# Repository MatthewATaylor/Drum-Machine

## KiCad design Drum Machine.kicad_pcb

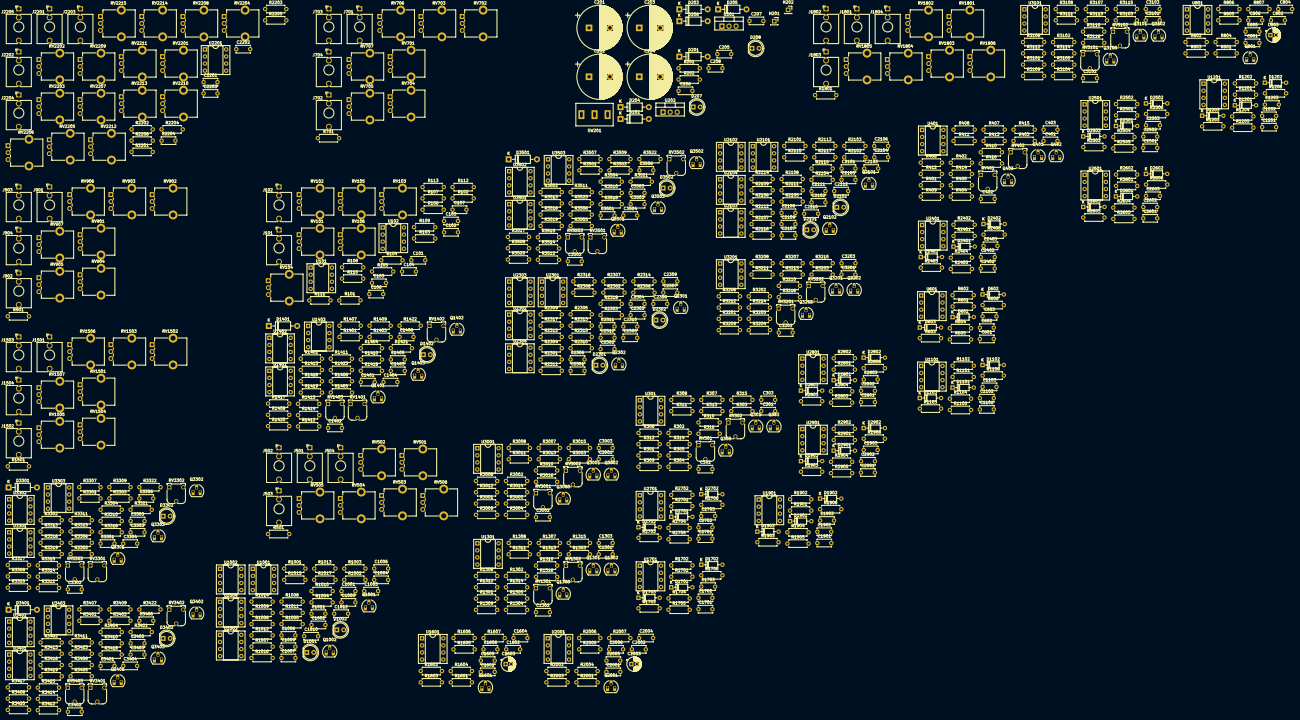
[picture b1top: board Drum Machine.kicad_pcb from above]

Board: 2 copper layers, 752 parts (0 on the bottom side), 443 nets, no tracks yet.

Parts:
C101, C601, C804, C1101, C1201, C1604, C1701, C1901, C2004, C2401, C2501, C2601, C2701, C2801, C2901: 10n; C_Disc_D5.0mm_W2.5mm_P5.00mm
C102, C103, C1008, C1011, C2108, C2111, C2201, C2308, C2311: 1n; C_Disc_D5.0mm_W2.5mm_P5.00mm
C104, C105, C106, C107, C301, C302, C401, C402, C602, C801, C802, C1002, C1003, C1004, C1005, C1006, C1007, C1009, C1010, C1102, C1202, C1301, C1302, C1401, C1402, C1403, C1404, C1405, C1406, C1601, C1602, C1702, C1902, C2001, C2002, C2102, C2103, C2104, C2105, C2106, C2107, C2109, C2110, C2202, C2203, C2204, C2302, C2303, C2304, C2305, C2306, C2307, C2309, C2310, C2402, C2502, C2602, C2702, C2802, C2902, C3001, C3002, C3101, C3102, C3201, C3202, C3301, C3302, C3303, C3304, C3305, C3306, C3401, C3402, C3403, C3404, C3405, C3406, C3501, C3502, C3503, C3504, C3505, C3506: 0.1u; C_Disc_D5.0mm_W2.5mm_P5.00mm
C201, C202, C203, C204: 2200u; CP_Radial_D16.0mm_P7.50mm
C205, C206, C207, C208: 1u; C_Disc_D5.0mm_W2.5mm_P5.00mm
C303, C403, C603, C1103, C1203, C1303, C1703, C1903, C2403, C2503, C2603, C2703, C2803, C2903, C3003, C3103, C3203: 10u; C_Disc_D5.0mm_W2.5mm_P5.00mm
C803, C1603, C2003: 100u; CP_Radial_D5.0mm_P2.00mm
C805, C806, C1605, C1606, C2005, C2006: 220n; C_Disc_D5.0mm_W2.5mm_P5.00mm
C1001, C2101, C2301: 4.7n; C_Disc_D5.0mm_W2.5mm_P5.00mm
C1012, C2112, C2312: 0.47u; C_Disc_D5.0mm_W2.5mm_P5.00mm
D201, D202, D203, D204, D205, D206, D1401, D3301, D3401, D3501: 1N5819; D_DO-41_SOD81_P10.16mm_Horizontal
D207, D208, D1001, D1002, D1402, D2101, D2102, D2301, D2302, D3302, D3402, D3502: LED; LED_D5.0mm
D601, D602, D603, D1101, D1102, D1103, D1201, D1202, D1203, D1701, D1702, D1703, D1901, D1902, D1903, D2401, D2402, D2403, D2501, D2502, D2503, D2601, D2602, D2603, D2701, D2702, D2703, D2801, D2802, D2803, D2901, D2902, D2903: 1N4148; D_DO-35_SOD27_P7.62mm_Horizontal
H201, H202: MountingHole_Pad; PinSocket_1x01_P2.54mm_Vertical
J101, J102, J501, J502, J503, J504, J701, J702, J703, J704, J901, J902, J903, J904, J1501, J1502, J1503, J1504, J1801, J1802, J1803, J1804, J2201, J2202, J2203, J2204, J2205: AudioJack2_SwitchT; Jack_3.5mm_QingPu_WQP-PJ398SM_Vertical_CircularHoles
Q301, Q302, Q303, Q401, Q402, Q403, Q1301, Q1302, Q1303, Q1401, Q1402, Q1403, Q3001, Q3002, Q3003, Q3101, Q3102, Q3103, Q3201, Q3202, Q3203, Q3301, Q3302, Q3303, Q3401, Q3402, Q3403, Q3501, Q3502, Q3503: 2N3904; TO-92_HandSolder
Q801, Q1601, Q2001: BC548; TO-92_HandSolder
Q1001, Q1002, Q2101, Q2102, Q2301, Q2302: BC558; TO-92_HandSolder
R101, R102, R103, R104, R105, R106, R107, R306, R406, R601, R602, R603, R604, R802, R803, R805, R1001, R1002, R1101, R1102, R1103, R1104, R1201, R1202, R1203, R1204, R1306, R1401, R1402, R1403, R1405, R1406, R1407, R1408, R1412, R1602, R1603, R1605, R1701, R1702, R1703, R1704, R1901, R1902, R1903, R1904, R2002, R2003, R2005, R2101, R2102, R2201, R2202, R2203, R2301, R2302, R2303, R2401, R2402, R2403, R2404, R2501, R2502, R2503, R2504, R2601, R2602, R2603, R2604, R2701, R2702, R2703, R2704, R2801, R2802, R2803, R2804, R2901, R2902, R2903, R2904, R3006, R3106, R3206, R3301, R3302, R3303, R3305, R3306, R3307, R3308, R3312, R3401, R3402, R3403, R3405, R3406, R3407, R3408, R3412, R3501, R3502, R3503, R3505, R3506, R3507, R3508, R3512: 100k; R_Axial_DIN0207_L6.3mm_D2.5mm_P7.62mm_Horizontal
R108, R110, R301, R401, R1301, R2204, R2205, R3001, R3101, R3201: 220k; R_Axial_DIN0207_L6.3mm_D2.5mm_P7.62mm_Horizontal
R109: 5.6k; R_Axial_DIN0207_L6.3mm_D2.5mm_P7.62mm_Horizontal
R111: 1.5k; R_Axial_DIN0207_L6.3mm_D2.5mm_P7.62mm_Horizontal
R112, R113, R302, R402, R501, R701, R901, R1302, R1501, R1801, R2206, R3002, R3102, R3202: 1k; R_Axial_DIN0207_L6.3mm_D2.5mm_P7.62mm_Horizontal
R201, R202: 33k; R_Axial_DIN0207_L6.3mm_D2.5mm_P7.62mm_Horizontal
R303, R304, R403, R404, R1303, R1304, R1411, R3003, R3004, R3103, R3104, R3203, R3204, R3311, R3411, R3511: 470k; R_Axial_DIN0207_L6.3mm_D2.5mm_P7.62mm_Horizontal
R305, R307, R405, R407, R1305, R1307, R3005, R3007, R3105, R3107, R3205, R3207: 150k; R_Axial_DIN0207_L6.3mm_D2.5mm_P7.62mm_Horizontal
R308, R311, R312, R315, R408, R411, R412, R415, R1308, R1311, R1312, R1315, R3008, R3011, R3012, R3015, R3108, R3111, R3112, R3115, R3208, R3211, R3212, R3215: 22k; R_Axial_DIN0207_L6.3mm_D2.5mm_P7.62mm_Horizontal
R309, R310, R316, R409, R410, R416, R1006, R1009, R1010, R1011, R1012, R1016, R1017, R1309, R1310, R1316, R1414, R1417, R2106, R2109, R2110, R2111, R2112, R2116, R2117, R2307, R2310, R2311, R2312, R2313, R2317, R2318, R3009, R3010, R3016, R3109, R3110, R3116, R3209, R3210, R3216, R3314, R3317, R3414, R3417, R3514, R3517: 10k; R_Axial_DIN0207_L6.3mm_D2.5mm_P7.62mm_Horizontal
R313, R314, R413, R414, R1004, R1313, R1314, R1410, R2104, R2305, R3013, R3014, R3113, R3114, R3213, R3214, R3310, R3410, R3510: 330k; R_Axial_DIN0207_L6.3mm_D2.5mm_P7.62mm_Horizontal
R605, R1105, R1205, R1416, R1705, R1905, R2405, R2505, R2605, R2705, R2805, R2905, R3316, R3416, R3516: 15k; R_Axial_DIN0207_L6.3mm_D2.5mm_P7.62mm_Horizontal
R606, R1106, R1206, R1706, R1906, R2406, R2506, R2606, R2706, R2806, R2906: 470; R_Axial_DIN0207_L6.3mm_D2.5mm_P7.62mm_Horizontal
R801, R804, R806, R1005, R1601, R1604, R1606, R2001, R2004, R2006, R2105, R2306: 4.7k; R_Axial_DIN0207_L6.3mm_D2.5mm_P7.62mm_Horizontal
R807, R1404, R1409, R1607, R2007, R3304, R3309, R3404, R3409, R3504, R3509: 47k; R_Axial_DIN0207_L6.3mm_D2.5mm_P7.62mm_Horizontal
R1003, R1014, R2103, R2114, R2304, R2315: 2.2k; R_Axial_DIN0207_L6.3mm_D2.5mm_P7.62mm_Horizontal
R1007, R1008, R1013, R1015, R1413, R2107, R2108, R2113, R2115, R2308, R2309, R2314, R2316, R3313, R3413, R3513: 220; R_Axial_DIN0207_L6.3mm_D2.5mm_P7.62mm_Horizontal
R1415, R3315, R3415, R3515: 330; R_Axial_DIN0207_L6.3mm_D2.5mm_P7.62mm_Horizontal
R1418, R1419, R3318, R3319, R3418, R3419, R3518, R3519: 7.5k; R_Axial_DIN0207_L6.3mm_D2.5mm_P7.62mm_Horizontal
R1420, R1421, R1422, R3320, R3321, R3322, R3420, R3421, R3422, R3520, R3521, R3522: 680k; R_Axial_DIN0207_L6.3mm_D2.5mm_P7.62mm_Horizontal
R1423, R3323, R3423, R3523: 75k; R_Axial_DIN0207_L6.3mm_D2.5mm_P7.62mm_Horizontal
RV101, RV102, RV103, RV104, RV105, RV106, RV501, RV502, RV503, RV504, RV505, RV506, RV701, RV702, RV703, RV706, RV707, RV901, RV902, RV903, RV906, RV907, RV1501, RV1502, RV1503, RV1506, RV1507, RV1801, RV1802, RV1803, RV1804, RV1805, RV1806, RV2202, RV2203, RV2204, RV2205, RV2206, RV2207, RV2208, RV2210, RV2211, RV2213, RV2214, RV2215: 50k; Potentiometer_Alpha_RD901F-40-00D_Single_Vertical_CircularH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
RV301, RV302, RV401, RV402, RV1301, RV1302, RV1401, RV1402, RV1403, RV3001, RV3002, RV3101, RV3102, RV3201, RV3202, RV3301, RV3302, RV3303, RV3401, RV3402, RV3403, RV3501, RV3502, RV3503: 10k; Potentiometer_Runtron_RM-065_Vertical_Improved
RV704, RV705, RV904, RV905, RV1504, RV1505: 1M; Potentiometer_Alpha_RD901F-40-00D_Single_Vertical_CircularH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
RV2201, RV2209, RV2212: 100k; Potentiometer_Alpha_RD901F-40-00D_Single_Vertical_CircularH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
SW201: SW_SPDT; MTS-102_MTS-103_MTS-112_MTS-113_MTS-123
U101, U102, U301, U401, U801, U1001, U1002, U1301, U1401, U1402, U1403, U1601, U2001, U2101, U2102, U2201, U2301, U2302, U3001, U3101, U3201, U3301, U3302, U3303, U3401, U3402, U3403, U3501, U3502, U3503: TL072; DIP-8_W7.62mm_Socket
U201: LM7812_TO220; TO-220-3_Vertical
U202: LM7912_TO220; TO-220-3_Vertical
U601, U1101, U1201, U1701, U1901, U2401, U2501, U2601, U2701, U2801, U2901: LM358; DIP-8_W7.62mm_Socket
U1003, U1004, U2103, U2104, U2303, U2304: CA3080; DIP-8_W7.62mm_Socket

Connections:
+12V: C104.1, C106.1, C207.1, C301.1, C401.1, C602.1, C801.1, C1002.1, C1004.1, C1007.2, C1010.2, C1102.1, C1202.1, C1301.1, C1401.1, C1403.1, C1405.1, C1601.1, C1702.1, C1902.1, C2001.1, C2102.1, C2104.1, C2107.2, C2110.2, C2202.1, C2302.1, C2304.1, C2307.2, C2310.2, C2402.1, C2502.1, C2602.1, C2702.1, C2802.1, C2902.1, C3001.1, C3101.1, C3201.1, C3301.1, C3303.1, C3305.1, C3401.1, C3403.1, C3405.1, C3501.1, C3503.1, C3505.1, D203.2 (A), D205.1 (K), D207.2 (A), R604.1, R801.1, R1104.1, R1204.1, R1414.1, R1417.1, R1601.1, R1704.1, R1904.1, R2001.1, R2404.1, R2504.1, R2604.1, R2704.1, R2804.1, R2904.1, R3314.1, R3317.1, R3414.1, R3417.1, R3514.1, R3517.1, RV301.2, RV302.1, RV401.2, RV402.1, RV501.1, RV702.1, RV902.1, RV1301.2, RV1302.1, RV1403.1, RV1502.1, RV1801.1, RV2203.1, RV2206.1, RV3001.2, RV3002.1, RV3101.2, RV3102.1, RV3201.2, RV3202.1, RV3303.1, RV3403.1, RV3503.1, U101.8 (V+), U102.8 (V+), U201.3 (VO), U301.8 (V+), U401.8 (V+), U601.8 (V+), U801.8 (V+), U1001.8 (V+), U1002.8 (V+), U1003.7 (V+), U1004.7 (V+), U1101.8 (V+), U1201.8 (V+), U1301.8 (V+), U1401.8 (V+), U1402.8 (V+), U1403.8 (V+), U1601.8 (V+), U1701.8 (V+), U1901.8 (V+), U2001.8 (V+), U2101.8 (V+), U2102.8 (V+), U2103.7 (V+), U2104.7 (V+), U2201.8 (V+), U2301.8 (V+), U2302.8 (V+), U2303.7 (V+), U2304.7 (V+), U2401.8 (V+), U2501.8 (V+), U2601.8 (V+), U2701.8 (V+), U2801.8 (V+), U2901.8 (V+), U3001.8 (V+), U3101.8 (V+), U3201.8 (V+), U3301.8 (V+), U3302.8 (V+), U3303.8 (V+), U3401.8 (V+), U3402.8 (V+), U3403.8 (V+), U3501.8 (V+), U3502.8 (V+), U3503.8 (V+)
-12V: C105.1, C107.1, C208.2, C302.1, C402.1, C802.1, C1003.1, C1005.1, C1006.2, C1009.2, C1302.1, C1402.1, C1404.1, C1406.1, C1602.1, C2002.1, C2103.1, C2105.1, C2106.2, C2109.2, C2203.1, C2303.1, C2305.1, C2306.2, C2309.2, C3002.1, C3102.1, C3202.1, C3302.1, C3304.1, C3306.1, C3402.1, C3404.1, C3406.1, C3502.1, C3504.1, C3506.1, D204.1 (K), D206.2 (A), D208.1 (K), R316.1, R416.1, R1004.2, R1316.1, R1416.2, R2104.2, R2305.2, R3016.1, R3116.1, R3216.1, R3316.2, R3416.2, R3516.2, RV501.3, RV1801.3, RV2206.3, U101.4 (V-), U102.4 (V-), U202.3 (VO), U301.4 (V-), U401.4 (V-), U801.4 (V-), U1001.4 (V-), U1002.4 (V-), U1003.4 (V-), U1004.4 (V-), U1301.4 (V-), U1401.4 (V-), U1402.4 (V-), U1403.4 (V-), U1601.4 (V-), U2001.4 (V-), U2101.4 (V-), U2102.4 (V-), U2103.4 (V-), U2104.4 (V-), U2201.4 (V-), U2301.4 (V-), U2302.4 (V-), U2303.4 (V-), U2304.4 (V-), U3001.4 (V-), U3101.4 (V-), U3201.4 (V-), U3301.4 (V-), U3302.4 (V-), U3303.4 (V-), U3401.4 (V-), U3402.4 (V-), U3403.4 (V-), U3501.4 (V-), U3502.4 (V-), U3503.4 (V-)
/BD/Amplitude Envelope/GATE: C2401.1, C2701.1, J901.T, R2401.1, R2701.1
/BD/Amplitude Envelope/OUT: RV906.1, U2401.6 (-), U2401.7
/BD/Amplitude Envelope/RELEASE_R_1: D2403.2 (A), RV905.1
/BD/Amplitude Envelope/RELEASE_R_2: C2403.1, D2402.1 (K), RV905.2, RV905.3, U2401.5 (+)
/BD/OUT: R901.1, R3014.2, RV101.3, U3001.7
/BD/Pitch Envelope/OUT: RV901.1, U2701.6 (-), U2701.7
/BD/Pitch Envelope/RELEASE_R_1: D2703.2 (A), RV904.1
/BD/Pitch Envelope/RELEASE_R_2: C2703.1, D2702.1 (K), RV904.2, RV904.3, U2701.5 (+)
/BD/TIMING_CAP_1: C101.1, R3307.2, R3309.1, U3301.6 (-)
/BD/TIMING_CAP_2: C101.2, U3301.7, U3302.2 (-), U3302.5 (+)
/BD/VCA/CV1: R3003.1, RV906.2
/BD/VCA/CV2: R3004.1, RV907.2
/BD/VCA/IN: C3003.1, R3319.2, R3320.2, U3303.1
/BD/VCO/CV1: R3301.1, RV901.2
/BD/VCO/CV2: R3302.1, RV902.2
/BD/VCO/CV3: R3303.1, RV903.2
/BD/VCO/TRI: RV3301.1, U3302.6 (-), U3302.7
/H1/Amplitude Envelope/GATE: C1901.1, J1801.T, R1901.1
/H1/Amplitude Envelope/OUT: RV1805.1, U1901.6 (-), U1901.7
/H1/Amplitude Envelope/RELEASE_R_1: D1903.2 (A), RV1804.1
/H1/Amplitude Envelope/RELEASE_R_2: C1903.1, D1902.1 (K), RV1804.2, RV1804.3, U1901.5 (+)
/H1/HPF/CV1: R2101.1, RV1801.2
/H1/HPF/CV2: R2102.1, RV1802.2
/H1/HPF/FB_IN: D2101.1 (K), D2102.2 (A), R2112.2, R2114.2, RV1803.2, U2102.5 (+), U2102.6 (-)
/H1/HPF/IN: C2111.2, R2007.2, U2001.7
/H1/HPF/OUT: C303.1, C2112.2, RV1803.3
/H1/OUT: R314.2, R1801.1, RV104.3, U301.7
/H1/VCA/CV1: R303.1, RV1805.2
/H1/VCA/CV2: R304.1, RV1806.2
/H2/Amplitude Envelope/GATE: C601.1, J501.T, R601.1
/H2/Amplitude Envelope/OUT: RV505.1, U601.6 (-), U601.7
/H2/Amplitude Envelope/RELEASE_R_1: D603.2 (A), RV504.1
/H2/Amplitude Envelope/RELEASE_R_2: C603.1, D602.1 (K), RV504.2, RV504.3, U601.5 (+)
/H2/HPF/CV1: R1001.1, RV501.2
/H2/HPF/CV2: R1002.1, RV502.2
/H2/HPF/FB_IN: D1001.1 (K), D1002.2 (A), R1012.2, R1014.2, RV503.2, U1002.5 (+), U1002.6 (-)
/H2/HPF/IN: C1011.2, R807.2, U801.7
/H2/HPF/OUT: C403.1, C1012.2, RV503.3
/H2/OUT: R414.2, R501.1, RV105.3, U401.7
/H2/VCA/CV1: R403.1, RV505.2
/H2/VCA/CV2: R404.1, RV506.2
/SD/Amplitude Envelope/GATE: C1101.1, C1201.1, C1701.1, J2201.T, R1101.1, R1201.1, R1701.1
/SD/Amplitude Envelope/OUT: RV2214.1, U1701.6 (-), U1701.7
/SD/Amplitude Envelope/RELEASE_R_1: D1703.2 (A), RV2212.1
/SD/Amplitude Envelope/RELEASE_R_2: C1703.1, D1702.1 (K), RV2212.2, RV2212.3, U1701.5 (+)
/SD/Filter Envelope/OUT: RV2205.1, U1101.6 (-), U1101.7
/SD/Filter Envelope/RELEASE_R_1: D1103.2 (A), RV2209.1
/SD/Filter Envelope/RELEASE_R_2: C1103.1, D1102.1 (K), RV2209.2, RV2209.3, U1101.5 (+)
/SD/LPF/CV1: R2301.1, RV2205.2
/SD/LPF/CV2: R2302.1, RV2206.2
/SD/LPF/CV3: R2303.1, RV2207.2
/SD/LPF/FB_IN: D2301.1 (K), D2302.2 (A), R2313.2, R2315.2, RV2208.2, U2302.5 (+), U2302.6 (-)
/SD/LPF/IN: R1607.2, R2307.1, U1601.7
/SD/LPF/OUT: C2312.2, RV2208.3, RV2211.3
/SD/OUT: R1314.2, R2206.1, RV106.3, U1301.7
/SD/Pitch Envelope/OUT: RV2202.1, U1201.6 (-), U1201.7
/SD/Pitch Envelope/RELEASE_R_1: D1203.2 (A), RV2201.1
/SD/Pitch Envelope/RELEASE_R_2: C1203.1, D1202.1 (K), RV2201.2, RV2201.3, U1201.5 (+)
/SD/VCA/CV1: R1303.1, RV2214.2
/SD/VCA/CV2: R1304.1, RV2215.2
/SD/VCA/IN: C1303.1, C2204.2, RV2213.1, RV2213.2
/SD/VCO/CV1: R1401.1, RV2202.2
/SD/VCO/CV2: R1402.1, RV2203.2
/SD/VCO/CV3: R1403.1, RV2204.2
/SD/VCO/SINE: R1419.2, R1420.2, RV2210.3, U1403.1
/SD/VCO/TIMING_CAP_1: C2201.2, R1407.2, R1409.1, U1401.6 (-)
/SD/VCO/TIMING_CAP_2: C2201.1, U1401.7, U1402.2 (-), U1402.5 (+)
/SD/VCO/TRI: RV1401.1, U1402.6 (-), U1402.7
/T1/Amplitude Envelope/GATE: C2501.1, C2801.1, J701.T, R2501.1, R2801.1
/T1/Amplitude Envelope/OUT: RV706.1, U2501.6 (-), U2501.7
/T1/Amplitude Envelope/RELEASE_R_1: D2503.2 (A), RV705.1
/T1/Amplitude Envelope/RELEASE_R_2: C2503.1, D2502.1 (K), RV705.2, RV705.3, U2501.5 (+)
/T1/OUT: R701.1, R3114.2, RV102.3, U3101.7
/T1/Pitch Envelope/OUT: RV701.1, U2801.6 (-), U2801.7
/T1/Pitch Envelope/RELEASE_R_1: D2803.2 (A), RV704.1
/T1/Pitch Envelope/RELEASE_R_2: C2803.1, D2802.1 (K), RV704.2, RV704.3, U2801.5 (+)
/T1/TIMING_CAP_1: C102.1, R3407.2, R3409.1, U3401.6 (-)
/T1/TIMING_CAP_2: C102.2, U3401.7, U3402.2 (-), U3402.5 (+)
/T1/VCA/CV1: R3103.1, RV706.2
/T1/VCA/CV2: R3104.1, RV707.2
/T1/VCA/IN: C3103.1, R3419.2, R3420.2, U3403.1
/T1/VCO/CV1: R3401.1, RV701.2
/T1/VCO/CV2: R3402.1, RV702.2
/T1/VCO/CV3: R3403.1, RV703.2
/T1/VCO/TRI: RV3401.1, U3402.6 (-), U3402.7
/T2/Amplitude Envelope/GATE: C2601.1, C2901.1, J1501.T, R2601.1, R2901.1
/T2/Amplitude Envelope/OUT: RV1506.1, U2601.6 (-), U2601.7
/T2/Amplitude Envelope/RELEASE_R_1: D2603.2 (A), RV1505.1
/T2/Amplitude Envelope/RELEASE_R_2: C2603.1, D2602.1 (K), RV1505.2, RV1505.3, U2601.5 (+)
/T2/OUT: R1501.1, R3214.2, RV103.3, U3201.7
/T2/Pitch Envelope/OUT: RV1501.1, U2901.6 (-), U2901.7
/T2/Pitch Envelope/RELEASE_R_1: D2903.2 (A), RV1504.1
/T2/Pitch Envelope/RELEASE_R_2: C2903.1, D2902.1 (K), RV1504.2, RV1504.3, U2901.5 (+)
/T2/TIMING_CAP_1: C103.1, R3507.2, R3509.1, U3501.6 (-)
/T2/TIMING_CAP_2: C103.2, U3501.7, U3502.2 (-), U3502.5 (+)
/T2/VCA/CV1: R3203.1, RV1506.2
/T2/VCA/CV2: R3204.1, RV1507.2
/T2/VCA/IN: C3203.1, R3519.2, R3520.2, U3503.1
/T2/VCO/CV1: R3501.1, RV1501.2
/T2/VCO/CV2: R3502.1, RV1502.2
/T2/VCO/CV3: R3503.1, RV1503.2
/T2/VCO/TRI: RV3501.1, U3502.6 (-), U3502.7
AC: H201.1, SW201.3 (C)
GND: C104.2, C105.2, C106.2, C107.2, C201.2, C202.1, C203.2, C204.1, C205.2, C206.1, C207.2, C208.1, C301.2, C302.2, C401.2, C402.2, C602.2, C603.2, C801.2, C802.2, C803.2, C805.1, C806.1, C1002.2, C1003.2, C1004.2, C1005.2, C1006.1, C1007.1, C1009.1, C1010.1, C1102.2, C1103.2, C1202.2, C1203.2, C1301.2, C1302.2, C1401.2, C1402.2, C1403.2, C1404.2, C1405.2, C1406.2, C1601.2, C1602.2, C1603.2, C1605.1, C1606.1, C1702.2, C1703.2, C1902.2, C1903.2, C2001.2, C2002.2, C2003.2, C2005.1, C2006.1, C2102.2, C2103.2, C2104.2, C2105.2, C2106.1, C2107.1, C2109.1, C2110.1, C2202.2, C2203.2, C2302.2, C2303.2, C2304.2, C2305.2, C2306.1, C2307.1, C2309.1, C2310.1, C2311.2, C2402.2, C2403.2, C2502.2, C2503.2, C2602.2, C2603.2, C2702.2, C2703.2, C2802.2, C2803.2, C2902.2, C2903.2, C3001.2, C3002.2, C3101.2, C3102.2, C3201.2, C3202.2, C3301.2, C3302.2, C3303.2, C3304.2, C3305.2, C3306.2, C3401.2, C3402.2, C3403.2, C3404.2, C3405.2, C3406.2, C3501.2, C3502.2, C3503.2, C3504.2, C3505.2, C3506.2, D205.2 (A), D206.1 (K), D601.2 (A), D1101.2 (A), D1201.2 (A), D1401.2 (A), D1402.2 (A), D1701.2 (A), D1901.2 (A), D2401.2 (A), D2501.2 (A), D2601.2 (A), D2701.2 (A), D2801.2 (A), D2901.2 (A), D3301.2 (A), D3302.2 (A), D3401.2 (A), D3402.2 (A), D3501.2 (A), D3502.2 (A), H202.1, J101.S, J102.S, J501.S, J502.S, J503.S, J504.S, J701.S, J702.S, J703.S, J704.S, J901.S, J902.S, J903.S, J904.S, J1501.S, J1502.S, J1503.S, J1504.S, J1801.S, J1802.S, J1803.S, J1804.S, J2201.S, J2202.S, J2203.S, J2204.S, J2205.S, Q302.2 (B), Q303.3 (C), Q402.2 (B), Q403.3 (C), Q801.2 (B), Q1002.2 (B), Q1302.2 (B), Q1303.3 (C), Q1401.1 (E), Q1403.2 (B), Q1601.2 (B), Q2001.2 (B), Q2102.2 (B), Q2302.2 (B), Q3002.2 (B), Q3003.3 (C), Q3102.2 (B), Q3103.3 (C), Q3202.2 (B), Q3203.3 (C), Q3301.1 (E), Q3303.2 (B), Q3401.1 (E), Q3403.2 (B), Q3501.1 (E), Q3503.2 (B), R111.2, R201.2, R202.1, R302.1, R313.2, R402.1, R413.2, R601.2, R603.1, R605.2, R803.2, R1003.2, R1006.1, R1007.2, R1008.2, R1013.2, R1014.1, R1015.2, R1101.2, R1103.1, R1105.2, R1201.2, R1203.1, R1205.2, R1302.1, R1313.2, R1404.2, R1408.2, R1410.1, R1413.2, R1418.1, R1603.2, R1701.2, R1703.1, R1705.2, R1901.2, R1903.1, R1905.2, R2003.2, R2103.2, R2106.1, R2107.2, R2108.2, R2113.2, R2114.1, R2115.2, R2304.2, R2308.2, R2309.2, R2314.2, R2315.1, R2316.2, R2401.2, R2403.1, R2405.2, R2501.2, R2503.1, R2505.2, R2601.2, R2603.1, R2605.2, R2701.2, R2703.1, R2705.2, R2801.2, R2803.1, R2805.2, R2901.2, R2903.1, R2905.2, R3002.1, R3013.2, R3102.1, R3113.2, R3202.1, R3213.2, R3304.2, R3308.2, R3310.1, R3313.2, R3318.1, R3404.2, R3408.2, R3410.1, R3413.2, R3418.1, R3504.2, R3508.2, R3510.1, R3513.2, R3518.1, RV101.1, RV102.1, RV103.1, RV104.1, RV105.1, RV106.1, RV302.3, RV402.3, RV502.3, RV503.1, RV505.3, RV506.3, RV701.3, RV702.3, RV703.3, RV706.3, RV707.3, RV901.3, RV902.3, RV903.3, RV906.3, RV907.3, RV1302.3, RV1403.3, RV1501.3, RV1502.3, RV1503.3, RV1506.3, RV1507.3, RV1802.3, RV1803.1, RV1805.3, RV1806.3, RV2202.3, RV2203.3, RV2204.3, RV2205.3, RV2207.3, RV2208.1, RV2210.1, RV2211.1, RV2213.3, RV2214.3, RV2215.3, RV3002.3, RV3102.3, RV3202.3, RV3303.3, RV3403.3, RV3503.3, SW201.1 (A), U101.3 (+), U101.5 (+), U201.2 (GND), U202.1 (GND), U301.3 (+), U401.3 (+), U601.4 (V-), U1001.3 (+), U1101.4 (V-), U1201.4 (V-), U1301.3 (+), U1403.5 (+), U1701.4 (V-), U1901.4 (V-), U2101.3 (+), U2201.3 (+), U2201.5 (+), U2301.3 (+), U2401.4 (V-), U2501.4 (V-), U2601.4 (V-), U2701.4 (V-), U2801.4 (V-), U2901.4 (V-), U3001.3 (+), U3101.3 (+), U3201.3 (+), U3303.5 (+), U3403.5 (+), U3503.5 (+)
unnamed: C201.1, C203.1, C205.1, D201.1 (K), D203.1 (K), U201.1 (VI)
unnamed: C202.2, C204.2, C206.2, D202.2 (A), D204.2 (A), U202.2 (VI)
unnamed: C303.2, R301.1
unnamed: C403.2, R401.1
unnamed: C601.2, D601.1 (K), R602.1
unnamed: C803.1, R801.2, R802.1
unnamed: C804.1, Q801.3 (E), R802.2
unnamed: C804.2, R803.1, U801.3 (+)
unnamed: C805.2, R804.2
unnamed: C806.2, R806.2
unnamed: C1001.1, U1001.2 (-)
unnamed: C1001.2, R1005.2, U1001.1
unnamed: C1008.1, U1001.5 (+), U1003.6
unnamed: C1008.2, D1001.2 (A), D1002.1 (K), R1012.1, U1002.7
unnamed: C1011.1, U1002.3 (+), U1004.6
unnamed: C1012.1, R1017.2, U1002.1, U1002.2 (-)
unnamed: C1101.2, D1101.1 (K), R1102.1
unnamed: C1201.2, D1201.1 (K), R1202.1
unnamed: C1303.2, R1301.1
unnamed: C1603.1, R1601.2, R1602.1
unnamed: C1604.1, Q1601.3 (E), R1602.2
unnamed: C1604.2, R1603.1, U1601.3 (+)
unnamed: C1605.2, R1604.2
unnamed: C1606.2, R1606.2
unnamed: C1701.2, D1701.1 (K), R1702.1
unnamed: C1901.2, D1901.1 (K), R1902.1
unnamed: C2003.1, R2001.2, R2002.1
unnamed: C2004.1, Q2001.3 (E), R2002.2
unnamed: C2004.2, R2003.1, U2001.3 (+)
unnamed: C2005.2, R2004.2
unnamed: C2006.2, R2006.2
unnamed: C2101.1, U2101.2 (-)
unnamed: C2101.2, R2105.2, U2101.1
unnamed: C2108.1, U2101.5 (+), U2103.6
unnamed: C2108.2, D2101.2 (A), D2102.1 (K), R2112.1, U2102.7
unnamed: C2111.1, U2102.3 (+), U2104.6
unnamed: C2112.1, R2117.2, U2102.1, U2102.2 (-)
unnamed: C2204.1, R2205.1, U2201.7
unnamed: C2301.1, U2301.2 (-)
unnamed: C2301.2, R2306.2, U2301.1
unnamed: C2308.1, U2301.5 (+), U2303.6
unnamed: C2308.2, D2301.2 (A), D2302.1 (K), R2313.1, U2302.7
unnamed: C2311.1, U2302.3 (+), U2304.6
unnamed: C2312.1, R2318.2, U2302.1, U2302.2 (-)
unnamed: C2401.2, D2401.1 (K), R2402.1
unnamed: C2501.2, D2501.1 (K), R2502.1
unnamed: C2601.2, D2601.1 (K), R2602.1
unnamed: C2701.2, D2701.1 (K), R2702.1
unnamed: C2801.2, D2801.1 (K), R2802.1
unnamed: C2901.2, D2901.1 (K), R2902.1
unnamed: C3003.2, R3001.1
unnamed: C3103.2, R3101.1
unnamed: C3203.2, R3201.1
unnamed: D201.2 (A), D202.1 (K), SW201.2 (B)
unnamed: D207.1 (K), R201.1
unnamed: D208.2 (A), R202.2
unnamed: D602.2 (A), D603.1 (K), R606.2
unnamed: D1102.2 (A), D1103.1 (K), R1106.2
unnamed: D1202.2 (A), D1203.1 (K), R1206.2
unnamed: D1401.1 (K), Q1401.2 (B), R1412.1
unnamed: D1402.1 (K), R1423.1
unnamed: D1702.2 (A), D1703.1 (K), R1706.2
unnamed: D1902.2 (A), D1903.1 (K), R1906.2
unnamed: D2402.2 (A), D2403.1 (K), R2406.2
unnamed: D2502.2 (A), D2503.1 (K), R2506.2
unnamed: D2602.2 (A), D2603.1 (K), R2606.2
unnamed: D2702.2 (A), D2703.1 (K), R2706.2
unnamed: D2802.2 (A), D2803.1 (K), R2806.2
unnamed: D2902.2 (A), D2903.1 (K), R2906.2
unnamed: D3301.1 (K), Q3301.2 (B), R3312.1
unnamed: D3302.1 (K), R3323.1
unnamed: D3401.1 (K), Q3401.2 (B), R3412.1
unnamed: D3402.1 (K), R3423.1
unnamed: D3501.1 (K), Q3501.2 (B), R3512.1
unnamed: D3502.1 (K), R3523.1
unnamed: J101.T, R110.1, R112.1, U102.3 (+)
unnamed: J102.T, R113.1
unnamed: J502.T, RV502.1
unnamed: J503.T, RV506.1
unnamed: J504.T, R501.2
unnamed: J702.T, RV703.1
unnamed: J703.T, RV707.1
unnamed: J704.T, R701.2
unnamed: J902.T, RV903.1
unnamed: J903.T, RV907.1
unnamed: J904.T, R901.2
unnamed: J1502.T, RV1503.1
unnamed: J1503.T, RV1507.1
unnamed: J1504.T, R1501.2
unnamed: J1802.T, RV1802.1
unnamed: J1803.T, RV1806.1
unnamed: J1804.T, R1801.2
unnamed: J2202.T, RV2204.1
unnamed: J2203.T, RV2207.1
unnamed: J2204.T, RV2215.1
unnamed: J2205.T, R2206.2
unnamed: Q301.1 (E), Q302.1 (E), R315.2
unnamed: Q301.2 (B), R301.2, R302.2
unnamed: Q301.3 (C), R305.1, R310.1
unnamed: Q302.3 (C), R307.1, R309.1
unnamed: Q303.1 (E), R315.1, R316.2
unnamed: Q303.2 (B), R311.2, R312.2
unnamed: Q401.1 (E), Q402.1 (E), R415.2
unnamed: Q401.2 (B), R401.2, R402.2
unnamed: Q401.3 (C), R405.1, R410.1
unnamed: Q402.3 (C), R407.1, R409.1
unnamed: Q403.1 (E), R415.1, R416.2
unnamed: Q403.2 (B), R411.2, R412.2
unnamed: Q1001.1 (C), R1004.1
unnamed: Q1001.2 (B), R1001.2, R1002.2, R1003.1
unnamed: Q1001.3 (E), Q1002.3 (E), R1005.1
unnamed: Q1002.1 (C), R1009.1, R1016.1
unnamed: Q1301.1 (E), Q1302.1 (E), R1315.2
unnamed: Q1301.2 (B), R1301.2, R1302.2
unnamed: Q1301.3 (C), R1305.1, R1310.1
unnamed: Q1302.3 (C), R1307.1, R1309.1
unnamed: Q1303.1 (E), R1315.1, R1316.2
unnamed: Q1303.2 (B), R1311.2, R1312.2
unnamed: Q1401.3 (C), R1409.2
unnamed: Q1402.1 (E), R1415.1, RV1402.3
unnamed: Q1402.2 (B), R1413.1, RV1401.2, RV1401.3
unnamed: Q1402.3 (C), R1414.2, R1418.2, U1403.3 (+)
unnamed: Q1403.1 (E), R1415.2, RV1402.1
unnamed: Q1403.3 (C), R1417.2, R1419.1, U1403.2 (-)
unnamed: Q2101.1 (C), R2104.1
unnamed: Q2101.2 (B), R2101.2, R2102.2, R2103.1
unnamed: Q2101.3 (E), Q2102.3 (E), R2105.1
unnamed: Q2102.1 (C), R2109.1, R2116.1
unnamed: Q2301.1 (C), R2305.1
unnamed: Q2301.2 (B), R2301.2, R2302.2, R2303.2, R2304.1
unnamed: Q2301.3 (E), Q2302.3 (E), R2306.1
unnamed: Q2302.1 (C), R2310.1, R2317.1
unnamed: Q3001.1 (E), Q3002.1 (E), R3015.2
unnamed: Q3001.2 (B), R3001.2, R3002.2
unnamed: Q3001.3 (C), R3005.1, R3010.1
unnamed: Q3002.3 (C), R3007.1, R3009.1
unnamed: Q3003.1 (E), R3015.1, R3016.2
unnamed: Q3003.2 (B), R3011.2, R3012.2
unnamed: Q3101.1 (E), Q3102.1 (E), R3115.2
unnamed: Q3101.2 (B), R3101.2, R3102.2
unnamed: Q3101.3 (C), R3105.1, R3110.1
unnamed: Q3102.3 (C), R3107.1, R3109.1
unnamed: Q3103.1 (E), R3115.1, R3116.2
unnamed: Q3103.2 (B), R3111.2, R3112.2
unnamed: Q3201.1 (E), Q3202.1 (E), R3215.2
unnamed: Q3201.2 (B), R3201.2, R3202.2
unnamed: Q3201.3 (C), R3205.1, R3210.1
unnamed: Q3202.3 (C), R3207.1, R3209.1
unnamed: Q3203.1 (E), R3215.1, R3216.2
unnamed: Q3203.2 (B), R3211.2, R3212.2
unnamed: Q3301.3 (C), R3309.2
unnamed: Q3302.1 (E), R3315.1, RV3302.3
unnamed: Q3302.2 (B), R3313.1, RV3301.2, RV3301.3
unnamed: Q3302.3 (C), R3314.2, R3318.2, U3303.3 (+)
unnamed: Q3303.1 (E), R3315.2, RV3302.1
unnamed: Q3303.3 (C), R3317.2, R3319.1, U3303.2 (-)
unnamed: Q3401.3 (C), R3409.2
unnamed: Q3402.1 (E), R3415.1, RV3402.3
unnamed: Q3402.2 (B), R3413.1, RV3401.2, RV3401.3
unnamed: Q3402.3 (C), R3414.2, R3418.2, U3403.3 (+)
unnamed: Q3403.1 (E), R3415.2, RV3402.1
unnamed: Q3403.3 (C), R3417.2, R3419.1, U3403.2 (-)
unnamed: Q3501.3 (C), R3509.2
unnamed: Q3502.1 (E), R3515.1, RV3502.3
unnamed: Q3502.2 (B), R3513.1, RV3501.2, RV3501.3
unnamed: Q3502.3 (C), R3514.2, R3518.2, U3503.3 (+)
unnamed: Q3503.1 (E), R3515.2, RV3502.1
unnamed: Q3503.3 (C), R3517.2, R3519.1, U3503.2 (-)
unnamed: R101.1, R102.1, R103.1, R104.1, R105.1, R106.1, R107.2, U101.2 (-)
unnamed: R101.2, RV101.2
unnamed: R102.2, RV102.2
unnamed: R103.2, RV103.2
unnamed: R104.2, RV104.2
unnamed: R105.2, RV105.2
unnamed: R106.2, RV106.2
unnamed: R107.1, R108.2, U101.1
unnamed: R108.1, R110.2, U101.6 (-)
unnamed: R109.1, U102.1, U102.2 (-)
unnamed: R109.2, R111.1, U102.5 (+)
unnamed: R112.2, U101.7
unnamed: R113.2, U102.6 (-), U102.7
unnamed: R303.2, R304.2, R306.1, U301.2 (-)
unnamed: R305.2, RV301.1
unnamed: R306.2, R308.1
unnamed: R307.2, RV301.3
unnamed: R308.2, R311.1, U301.1
unnamed: R309.2, R313.1, U301.5 (+)
unnamed: R310.2, R314.1, U301.6 (-)
unnamed: R312.1, RV302.2
unnamed: R403.2, R404.2, R406.1, U401.2 (-)
unnamed: R405.2, RV401.1
unnamed: R406.2, R408.1
unnamed: R407.2, RV401.3
unnamed: R408.2, R411.1, U401.1
unnamed: R409.2, R413.1, U401.5 (+)
unnamed: R410.2, R414.1, U401.6 (-)
unnamed: R412.1, RV402.2
unnamed: R602.2, R603.2, U601.3 (+)
unnamed: R604.2, R605.1, U601.2 (-)
unnamed: R606.1, U601.1
unnamed: R804.1, R805.1, U801.2 (-)
unnamed: R805.2, U801.1, U801.5 (+)
unnamed: R806.1, R807.1, U801.6 (-)
unnamed: R1006.2, R1007.1, R1010.1, U1003.2 (-)
unnamed: R1008.1, U1003.3 (+)
unnamed: R1009.2, U1003.5 (BIAS)
unnamed: R1010.2, R1011.1, U1001.6 (-), U1001.7
unnamed: R1011.2, R1015.1, U1004.3 (+)
unnamed: R1013.1, R1017.1, U1004.2 (-)
unnamed: R1016.2, U1004.5 (BIAS)
unnamed: R1102.2, R1103.2, U1101.3 (+)
unnamed: R1104.2, R1105.1, U1101.2 (-)
unnamed: R1106.1, U1101.1
unnamed: R1202.2, R1203.2, U1201.3 (+)
unnamed: R1204.2, R1205.1, U1201.2 (-)
unnamed: R1206.1, U1201.1
unnamed: R1303.2, R1304.2, R1306.1, U1301.2 (-)
unnamed: R1305.2, RV1301.1
unnamed: R1306.2, R1308.1
unnamed: R1307.2, RV1301.3
unnamed: R1308.2, R1311.1, U1301.1
unnamed: R1309.2, R1313.1, U1301.5 (+)
unnamed: R1310.2, R1314.1, U1301.6 (-)
unnamed: R1312.1, RV1302.2
unnamed: R1401.2, R1402.2, R1403.2, U1401.3 (+)
unnamed: R1404.1, R1405.1, U1401.2 (-)
unnamed: R1405.2, R1406.1, R1407.1, U1401.1
unnamed: R1406.2, R1408.1, U1401.5 (+)
unnamed: R1410.2, R1411.1, U1402.3 (+)
unnamed: R1411.2, R1412.2, U1402.1
unnamed: R1416.1, RV1402.2
unnamed: R1420.1, R1421.1, R1422.2, U1403.6 (-)
unnamed: R1421.2, RV1403.2
unnamed: R1422.1, R1423.2, U1403.7
unnamed: R1604.1, R1605.1, U1601.2 (-)
unnamed: R1605.2, U1601.1, U1601.5 (+)
unnamed: R1606.1, R1607.1, U1601.6 (-)
unnamed: R1702.2, R1703.2, U1701.3 (+)
unnamed: R1704.2, R1705.1, U1701.2 (-)
unnamed: R1706.1, U1701.1
unnamed: R1902.2, R1903.2, U1901.3 (+)
unnamed: R1904.2, R1905.1, U1901.2 (-)
unnamed: R1906.1, U1901.1
unnamed: R2004.1, R2005.1, U2001.2 (-)
unnamed: R2005.2, U2001.1, U2001.5 (+)
unnamed: R2006.1, R2007.1, U2001.6 (-)
unnamed: R2106.2, R2107.1, R2110.1, U2103.2 (-)
unnamed: R2108.1, U2103.3 (+)
unnamed: R2109.2, U2103.5 (BIAS)
unnamed: R2110.2, R2111.1, U2101.6 (-), U2101.7
unnamed: R2111.2, R2115.1, U2104.3 (+)
unnamed: R2113.1, R2117.1, U2104.2 (-)
unnamed: R2116.2, U2104.5 (BIAS)
unnamed: R2201.1, R2202.1, R2203.2, U2201.2 (-)
unnamed: R2201.2, RV2210.2
unnamed: R2202.2, RV2211.2
unnamed: R2203.1, R2204.2, U2201.1
unnamed: R2204.1, R2205.2, U2201.6 (-)
unnamed: R2307.2, R2308.1, R2311.1, U2303.2 (-)
unnamed: R2309.1, U2303.3 (+)
unnamed: R2310.2, U2303.5 (BIAS)
unnamed: R2311.2, R2312.1, U2301.6 (-), U2301.7
unnamed: R2312.2, R2316.1, U2304.3 (+)
unnamed: R2314.1, R2318.1, U2304.2 (-)
unnamed: R2317.2, U2304.5 (BIAS)
unnamed: R2402.2, R2403.2, U2401.3 (+)
unnamed: R2404.2, R2405.1, U2401.2 (-)
unnamed: R2406.1, U2401.1
unnamed: R2502.2, R2503.2, U2501.3 (+)
unnamed: R2504.2, R2505.1, U2501.2 (-)
unnamed: R2506.1, U2501.1
unnamed: R2602.2, R2603.2, U2601.3 (+)
unnamed: R2604.2, R2605.1, U2601.2 (-)
unnamed: R2606.1, U2601.1
unnamed: R2702.2, R2703.2, U2701.3 (+)
unnamed: R2704.2, R2705.1, U2701.2 (-)
unnamed: R2706.1, U2701.1
unnamed: R2802.2, R2803.2, U2801.3 (+)
unnamed: R2804.2, R2805.1, U2801.2 (-)
unnamed: R2806.1, U2801.1
unnamed: R2902.2, R2903.2, U2901.3 (+)
unnamed: R2904.2, R2905.1, U2901.2 (-)
unnamed: R2906.1, U2901.1
unnamed: R3003.2, R3004.2, R3006.1, U3001.2 (-)
unnamed: R3005.2, RV3001.1
unnamed: R3006.2, R3008.1
unnamed: R3007.2, RV3001.3
unnamed: R3008.2, R3011.1, U3001.1
unnamed: R3009.2, R3013.1, U3001.5 (+)
unnamed: R3010.2, R3014.1, U3001.6 (-)
unnamed: R3012.1, RV3002.2
unnamed: R3103.2, R3104.2, R3106.1, U3101.2 (-)
unnamed: R3105.2, RV3101.1
unnamed: R3106.2, R3108.1
unnamed: R3107.2, RV3101.3
unnamed: R3108.2, R3111.1, U3101.1
unnamed: R3109.2, R3113.1, U3101.5 (+)
unnamed: R3110.2, R3114.1, U3101.6 (-)
unnamed: R3112.1, RV3102.2
unnamed: R3203.2, R3204.2, R3206.1, U3201.2 (-)
unnamed: R3205.2, RV3201.1
unnamed: R3206.2, R3208.1
unnamed: R3207.2, RV3201.3
unnamed: R3208.2, R3211.1, U3201.1
unnamed: R3209.2, R3213.1, U3201.5 (+)
unnamed: R3210.2, R3214.1, U3201.6 (-)
unnamed: R3212.1, RV3202.2
unnamed: R3301.2, R3302.2, R3303.2, U3301.3 (+)
unnamed: R3304.1, R3305.1, U3301.2 (-)
unnamed: R3305.2, R3306.1, R3307.1, U3301.1
unnamed: R3306.2, R3308.1, U3301.5 (+)
unnamed: R3310.2, R3311.1, U3302.3 (+)
unnamed: R3311.2, R3312.2, U3302.1
unnamed: R3316.1, RV3302.2
unnamed: R3320.1, R3321.1, R3322.2, U3303.6 (-)
unnamed: R3321.2, RV3303.2
unnamed: R3322.1, R3323.2, U3303.7
unnamed: R3401.2, R3402.2, R3403.2, U3401.3 (+)
unnamed: R3404.1, R3405.1, U3401.2 (-)
unnamed: R3405.2, R3406.1, R3407.1, U3401.1
unnamed: R3406.2, R3408.1, U3401.5 (+)
unnamed: R3410.2, R3411.1, U3402.3 (+)
unnamed: R3411.2, R3412.2, U3402.1
unnamed: R3416.1, RV3402.2
unnamed: R3420.1, R3421.1, R3422.2, U3403.6 (-)
unnamed: R3421.2, RV3403.2
unnamed: R3422.1, R3423.2, U3403.7
unnamed: R3501.2, R3502.2, R3503.2, U3501.3 (+)
unnamed: R3504.1, R3505.1, U3501.2 (-)
unnamed: R3505.2, R3506.1, R3507.1, U3501.1
unnamed: R3506.2, R3508.1, U3501.5 (+)
unnamed: R3510.2, R3511.1, U3502.3 (+)
unnamed: R3511.2, R3512.2, U3502.1
unnamed: R3516.1, RV3502.2
unnamed: R3520.1, R3521.1, R3522.2, U3503.6 (-)
unnamed: R3521.2, RV3503.2
unnamed: R3522.1, R3523.2, U3503.7

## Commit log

2022-01-31 Create LICENSE
2022-01-31 Remove backup file
2022-02-01 Finish schematic
2022-02-01 Update VCO
2022-02-08 Finish PCB
2022-02-08 Resize panel
